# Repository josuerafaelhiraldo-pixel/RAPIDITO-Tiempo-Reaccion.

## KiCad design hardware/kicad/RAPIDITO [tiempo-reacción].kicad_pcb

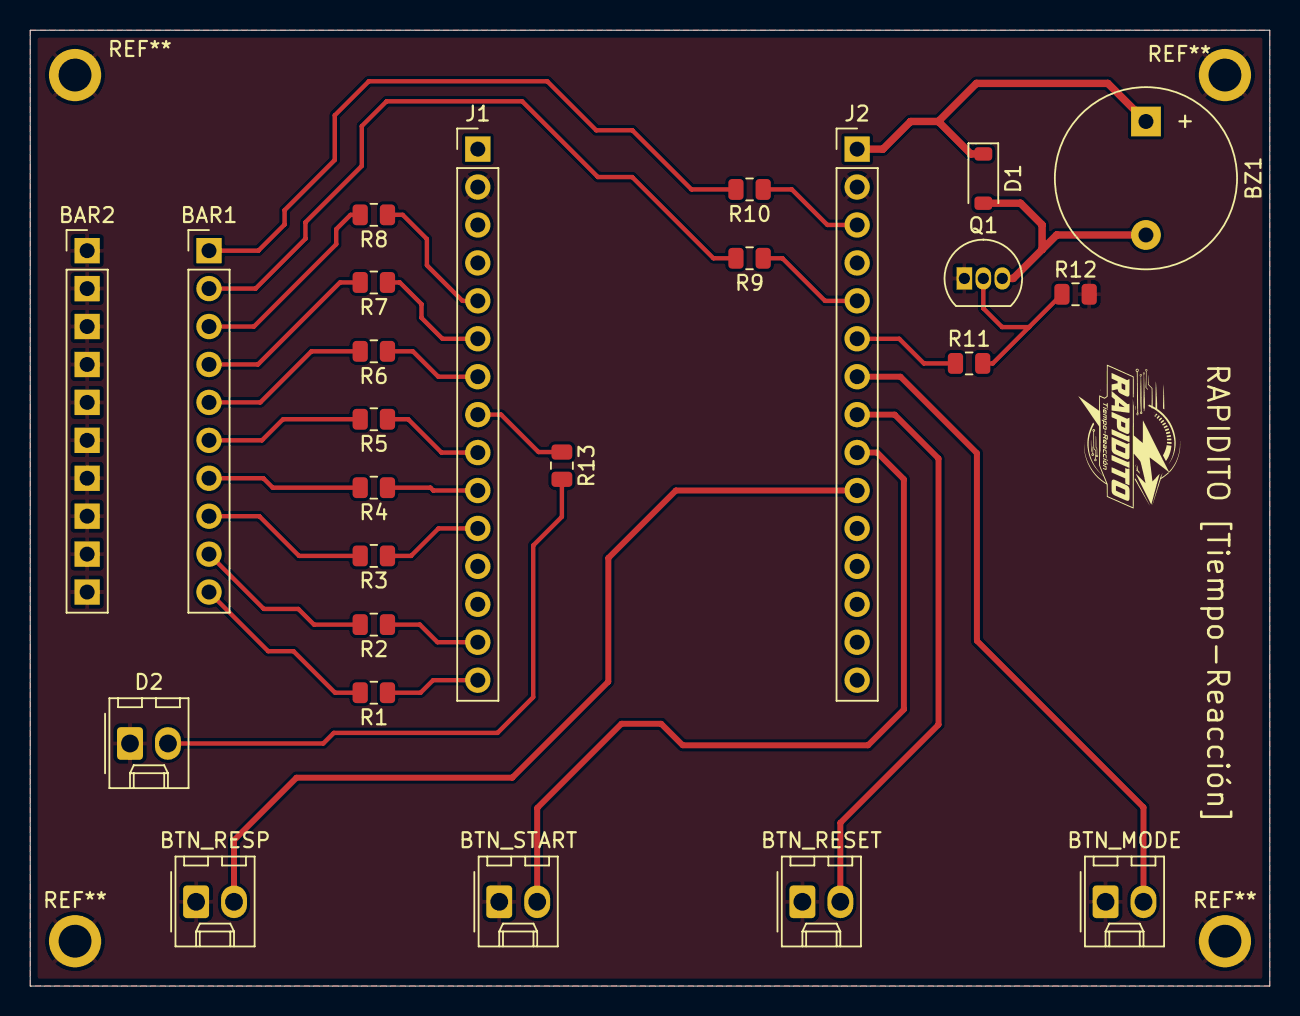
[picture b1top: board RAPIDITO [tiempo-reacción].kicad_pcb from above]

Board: 2 copper layers, 83.0 x 64.0 mm, 25 parts (0 on the bottom side), 31 nets.

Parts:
BAR1, BAR2: HDSP-4830_2; PinHeader_1x10_P2.54mm_Vertical
BTN_MODE: PB4; Molex_KK-254_AE-6410-02A_1x02_P2.54mm_Vertical
BTN_RESET: PB3; Molex_KK-254_AE-6410-02A_1x02_P2.54mm_Vertical
BTN_RESP: PB1; Molex_KK-254_AE-6410-02A_1x02_P2.54mm_Vertical
BTN_START: PB2; Molex_KK-254_AE-6410-02A_1x02_P2.54mm_Vertical
BZ1: Buzzer; Buzzer_12x9.5RM7.6
D1: 1N4001; D_SOD-123
D2: LED; Molex_KK-254_AE-6410-02A_1x02_P2.54mm_Vertical
J1, J2: Screw_Terminal_01x15; PinHeader_1x15_P2.54mm_Vertical
Q1: 2N3904; TO-92_Inline
R1, R2, R3, R4, R5, R6, R7, R8, R9, R10, R13: 330Ω; R_0805_2012Metric
R11: 1kΩ; R_0805_2012Metric
R12: 10kΩ; R_0805_2012Metric

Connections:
BUZZER: J2.6, R11.1
GND: BAR2.1 (A), BAR2.2 (A), BAR2.3 (A), BAR2.4 (A), BAR2.5 (A), BAR2.6 (A), BAR2.7 (A), BAR2.8 (A), BAR2.9 (A), BAR2.10 (A), BTN_MODE.1, BTN_RESET.1, BTN_RESP.1, BTN_START.1, D2.1 (K), J1.2, J2.2, Q1.1 (E), R12.2
LED1: J1.15, R1.1
LED2: J1.14, R2.1
LED3: J1.11, R3.1
LED4: J1.10, R4.1
LED5: J1.9, R5.1
LED6: J1.7, R6.1
LED7: J1.6, R7.1
LED8: J1.5, R8.1
LED9: J2.5, R9.1
LED10: J2.3, R10.1
LED_MODE: J1.8, R13.1
MODE_input: BTN_MODE.2, J2.7
unnamed: BAR1.1 (A), R10.2
unnamed: BAR1.2 (A), R9.2
unnamed: BAR1.3 (A), R8.2
unnamed: BAR1.4 (A), R7.2
unnamed: BAR1.5 (A), R6.2
unnamed: BAR1.6 (A), R5.2
unnamed: BAR1.7 (A), R4.2
unnamed: BAR1.8 (A), R3.2
unnamed: BAR1.9 (A), R2.2
unnamed: BAR1.10 (A), R1.2
unnamed: BZ1.2 (-), D1.2 (A), Q1.3 (C)
unnamed: D2.2 (A), R13.2
unnamed: Q1.2 (B), R11.2, R12.1
RESET_input: BTN_RESET.2, J2.8
RESP_input: BTN_RESP.2, J2.10
START_input: BTN_START.2, J2.9
VCC_5V: BZ1.1 (+), D1.1 (K), J2.1
